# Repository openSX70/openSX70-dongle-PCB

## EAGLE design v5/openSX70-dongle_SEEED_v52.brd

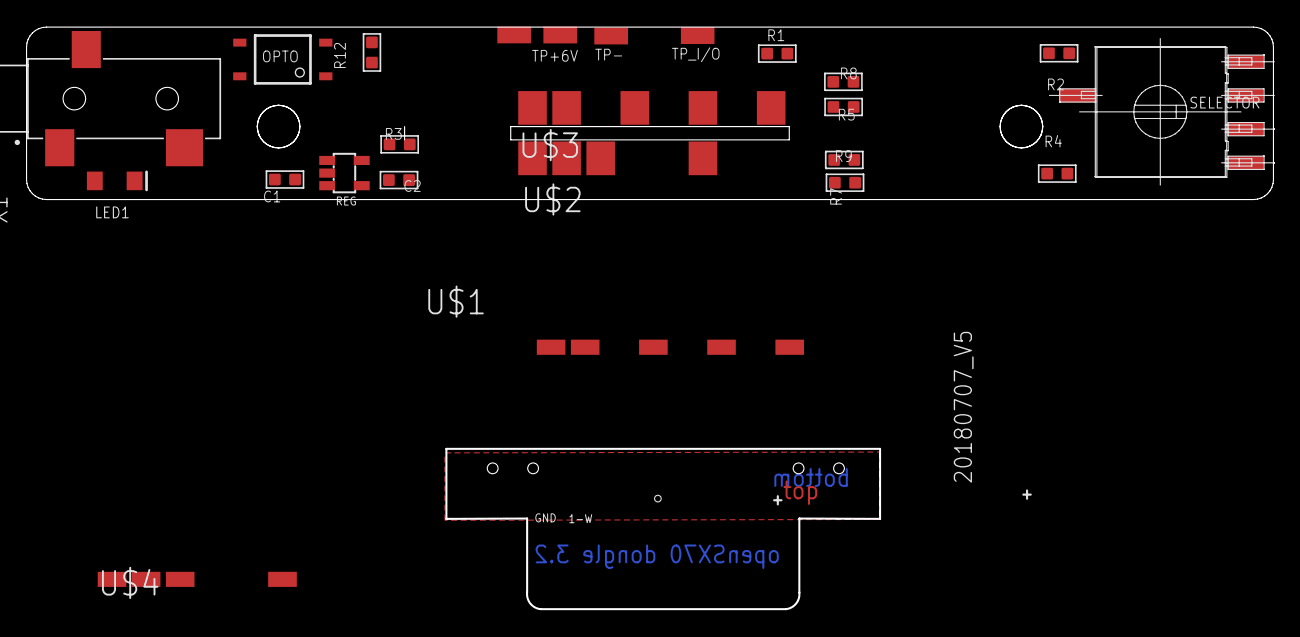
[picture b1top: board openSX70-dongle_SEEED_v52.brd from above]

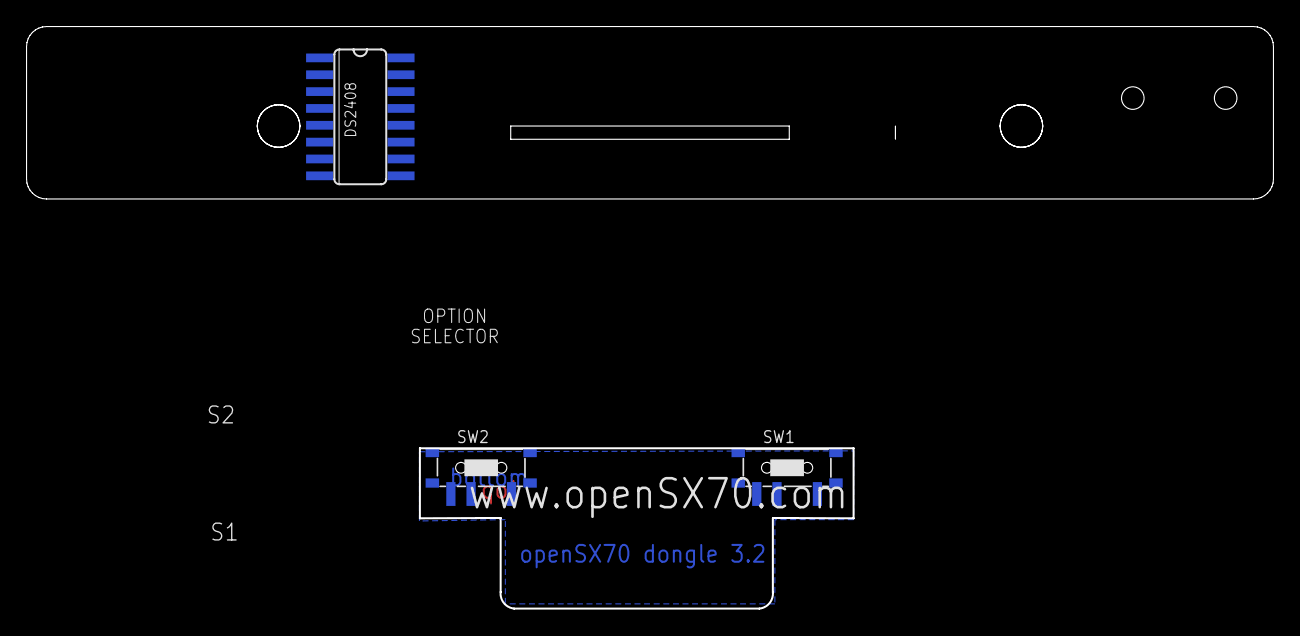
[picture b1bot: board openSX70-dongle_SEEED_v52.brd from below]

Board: 2 copper layers, 94.0 x 13.0 mm, 27 parts (3 on the bottom side), 18 nets, no tracks yet.

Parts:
C1, C2: 1uf; C0603
DS2408: DS2408; SO16
LED1: Yellow; LED-1206
OPTO: TLP127; SO-4
R1: 4.7K; R0603
R2, R3, R4, R5, R7, R8: 100K; R0603
R9, R12: 220R; R0603
REG: NCP4688; SOT-23-5
SELECTOR: SELECTOR-4-1-SMD-A6RS; A6RS-161RS
SW1, SW2: MK-12C02 G1.5; SW7-SMD-L6.7X2.7X3.2MM
TP+2.8V, TP+6V: SMD1,27-2,54
TP-: SMD1,27-2,54
TP_I/O: SMD1,27-2,54
U$1: FLASH-BRIDGE-SW1-SW2-LED-SMALL; FLASH-8-BRIDGE-SW1-SW2-LED-SMALL
U$2: FLASH-BRIDGE1; FLASH-8-BRIDGE1
U$3: FLASH-BRIDGE-SW1-SW2-LED; FLASH-8-BRIDGE-SW1-SW2-LED
U$4: FLASH-BRIDGE-SMALL; FLASH-8-BRIDGE1-SMALL
X1: JACK-SMD-SJ-3523-SMT-TR; CUI_SJ-3523-SMT-TR

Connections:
1-WIRE: DS2408.4, R1.1, TP_I/O.1, U$2.S2
2.8V: C2.1, DS2408.3, DS2408.10, OPTO.1, R1.2, REG.5, SELECTOR.C, TP+2.8V.1, U$3.VCC-2.8V
2.8V-V: SW1.A, SW2.A
GND: C1.2, C2.2, DS2408.5, R2.2, R3.1, R4.1, R5.1, R7.2, R8.2, REG.2, TP-.1, U$2.GND, U$3.GND
LED: LED1.A, U$3.LED
unnamed: OPTO.3, X1.1
unnamed: LED1.C, R9.2
unnamed: DS2408.2, R2.1, SELECTOR.8
unnamed: DS2408.14, R3.2, SELECTOR.4
unnamed: DS2408.13, R4.2, SELECTOR.2
unnamed: DS2408.8, R9.1
unnamed: OPTO.4, X1.2, X1.3
unnamed: OPTO.2, R12.2
unnamed: DS2408.7, R12.1
unnamed: DS2408.12, R5.2, SELECTOR.1
SWITCH-1: DS2408.9, R8.1, U$3.SWITCH-1
SWITCH-2: DS2408.11, R7.1, U$3.SWITCH-2
VCC-6V: C1.1, REG.1, REG.3, TP+6V.1, U$2.VCC-6V

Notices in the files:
parts and their libraries:
SparkFun-LED: Licensing: Creative Commons ShareAlike 4.0 International - https://creativecommons.org/licenses/by-sa/4.0
